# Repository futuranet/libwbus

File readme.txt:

== Disclaimer ==

This document contains information that might be wrong, not serve any
purpose or perhaps cause direct or indirect damage to any person. I cannot
be held responsible for anything in regard to this text document, the
accompanied documents or anything else related. Its all your own fault.

Any reference to any trade mark mentioned here or in the accompanied
documents are owned by their corresponding owners.

== What is this ? ==

A collection of W-Bus related libraries and programs for x86 and embedded
microcontroller devices.

== What is W-Bus ? ==

W-Bus is the serial line protocol used by Webasto (tm) car parking and
suplemental heating devices to communicate to a remote control or timer
unit, and also to performe PC assisted diagnosis of the device. This
interface is available on many modern Webasto (tm) heater devices.

== What W-Bus devices are supported to communicate to ? ==

Basic packet communication to any W-Bus capable device should be feasible.
Command codes, addresses or transaction IDs (how name them ?) are only known
so far for Thermo Top V heater devices. Some data has been discovered in
regard to the "1533" timer command devices and in the source forge forum
somebody also found some data in regard to Telestart (tm) receivers. I do
not own such devices so I cannot test anything in regard to that. Software
patches to add support for other devices are gladly accepted as long as the
changes do not add extra resource costs to the existing functionality and do
not include any unnecessary changes. Any patch containing "beautifications"
or any non functional changes will land directly in /dev/null. Don't loose
the point ;)

== What hardware does this software iself run on ? ==

The libwbus library and all its bundled applications should run on x86 Posix
like environment and MSP430 microcontrollers out of the box. Windows support
without cygwin is somewhat supported but there are known missing/broken
things.
Adapting the software for other targets should not be that difficult, just
grab an existing implementation and change it as necessary. For the hardware
and platform specific parts there are source code files using ad hoc
suffixes, and these source code files are included from source code files
without that suffixes. Just take a look and you will find out that quickly.
Doing this way, its not required changing makefiles or anything else to
switch hardware/platform, and thus only compiler built in macros should be
used to detect a given hardware or platform.

== K-Line adapter hardware ==
A K-Line is nothing but a single line serial connection, using a open
colector transistor that pulls a 12 Volt line to ground for mark bits.
At iddle, the line is at 12 Volt. As a pull up, 1Kohm should work ok.
See k_line.png for an example. The nets marked as TX and RX go to the
corresponding microcontroller serial port pins. The schematic shows an
example where the uC has 3.3 Volt I/O. You may need to adapt the voltage
levels depending on what hardware you do use.

== What is that Can-Bus thing ? ==

CAN-BUS is a network protocol for Controller Area Networks (hence the name).
It is widely used in the automotive world for communication between
different controller equipments.
Some people say that some Webasto (tm) devices can't be accessed through
W-Bus but only Can-Bus. That is not true, those devices are programmed at
the factory as suplemental heaters only, thus wont accept a parking heater
command on the W-Bus wire, but all others.
Possibly the reason is to avoid any cheap upgrade to a parking heater being
done by smart customers. Depending on for which car the heater was intended
the parking heater functionality might be enabled or not. From the hardware
perspective suplemental heaters and parking heater are identical AFAIK. The
firmware is different; this can be observed in the "W-Bus code" number.
Some car manufacturers sell upgrade packages which include a single use
dongle to enable parking heater functionality in suplemental heaters.

== Do you have a crack for the upgrade software dongle ? ==

No, I do not.
Its much easier to sell a suplemental heater on some auction house and buy
a parking heater for the same money.

== What is included in the repository ? ==

This software package comprises the following programs:

- openegg: W-Bus heater control unit targeted to a slightly modified MTK449
  olimex kit board. Schematics available on request, but I'm planning to
  rework the hardware at some point, but also using a MSP430 uC.
    The device when completely assembled provides through a menu driven UI the
  possibility to set 3 timers to turn on a W-Bus heater device. It also
  allows to select the command to be used, either parking heating,
  suplemental heating or ventilation.
  The heater can be turned on explicitly as well.
    Also it includes the function to connect a GSM mobile phone supporting
  the caller-ID AT commands, to program upto to 4 phone numbers to be
  authorized to turn on a W-Bus heater by calling the connected GSM mobile
  phone. The phone wont pick up the call, merely read out the caller ID number,
  thus no phone cost should ocurr.

- util/wbtool: a command line tool intended to be used on a PC or similar posix
  compatible system, to interact with a W-Bus device. Currently it supports
  all libwbus commands, thus turn on/off heater, read sensors, device ID
  data, etc.

- util/wbsim: a rudimentary and simple W-Bus device simulator mostly useful for
  understanding W-Bus and testing. In the W-Bus sense, its the counter part
  of wbtool.

- poeli: This program is intended to be used on an embedded heater device
  controller. It is designed for syphon nozzle atomizing burners with a
  nozzle stock heater, glow plug for ignition and flame monitoring,
  combustion air fan, nozzle air pressure compressor, 2 temperatur sensors,
  heat exchanger circulation pump, pulsed fuel pump (as usual in parking
  heaters), vehicle cabin fan output, and an auxiliar output. It acts as a
  W-Bus heater device, thus can be controlled and monitored using the
  Webasto (tm) Data Top (tm) software.
  A sequencer which is programmable via W-Bus protocol as well defines the
  course of action once a "heater on" or ventilation command is issued. Also
  the regular W-Bus component test commands and CO2 calibration are
  supported. The "program" can also be built and run on a PC for simulation
  purposes. See htsim.
  Circuit schematics are not included in the repository, and I'm not sure if
  I should really publish them. If you have any interest building a heater
  device, post it in the source forge forum, maybe there is some way to help
  you in that case. Heater device do burn fuel producing some kilo watt of
  heat and thus are DANGEROUS. Unless you plan to do something really stupid
  you are better off buying a ready made heater, building one is by far more
  expensive (easily a factor 4 of the price of an off the shelf device).

- bin/htsim: Heater device sensor / actuator simulator. A very simple basic
  and inaccurate model of a heater device. It uses shared memory to communicate
  to an instance of "poeli". It takes actuator values and generates data for
  the sensors. For example if the fuel pump is turned on, the simulator
  assumes combustion and will slowly rise the water temperatur sensor value
  and flame detector.

- util/htsim_gui: Same as htsim but interactive. Allows changing sensor
  values and watching actuator values via shared memory from an instance of
  "poeli". Since clicking on scrollbars takes a lot of time, rather less
  usefull. I never used it really, htsim turned out to be much more
  practical. Uses GTK+ and glade. Must be run from the "util" directory in
  order that the program can find its GUI description XML file.

- util/seq_edit: This programm allows to change almost all parameters of the
  poeli sequencer and read and write them via W-Bus to a heater device. This
  is not compatible with original Webasto (tm) heaters, since I do not know if
  and how they can be reprogrammed in this sense.

Libraries and others:

- libwbus: the wbus protocol handling library. see include/wbus.h for the
  client side API and include/wbus_server.h for the server side API.

- kernel: small cooperative multitasking micro kernel, to enable small
  microcontrollers to execute several tasks and blocking i/o. It also
  manages hardware abstraction in order to minimize the effort to port the
  whole software package to other processor architectures. Only 2-3 hardware
  specific lines of code.

- util/serial_loop: Linux kernel module which simulates 8 serial ports,
  which are looped back pairwise. It supports optional local echo, as it
  is the case in a K-Line or W-Bus line. It creates 8 device nodes called
  /dev/ttySL0 upto /dev/ttySL7, where /dev/ttySL0 is linked with
  /dev/ttySL1, and /dev/ttySL2 with /dev/ttySL3 and so on.
  The module should built with any recent 2.6 Linux kernel.

- Matlab files and excel spreadsheets: design blueprints and simulations
  that were used during the design and tuning of different parts of the
  heater device project. The Matlab files can be run directly as programs
  from a shell of GNU/Octave is installed.

== How do I compile this shit ? ==

Native compile:

make

Cross compile for MSP430f169:

make ARCH=msp430x169

To compile with debug symbols add DEBUG=1 to the command line.

the executables will be placed in bin<architecture name>, thus in
"binmsp430x169" for the example above. In case of native built in the folder
"bin".

The seq-edit and htsim_gui executables will be placed in util/ by the make
file, since it requires to load an XML file which is located there. Those
programs should be executed using util/ as working directory as well.

== How do I port this to my favorit uC since I hate that shitty MSP430 ? ==

- Re implement the functions and macros declared in the files rs232.h and
machine.h for your uC. Take the "posix" built variant as a template.
- Then put the implemention of that functions in new files called
rs232_myuc.c and machine_myuc.c. Where "myuc" somehow identifies your new uC
architechture or built environment. For example rs232_avr.c ...
- Make sure that those files are inluded in rs232.c and machine.c in case
your compiler for your uC is being used (consult predefined macros of your
compiler)
- Change the the Makefile CFLAGS and LDFLAGS if required.
- If you do not break functionality nor compilability for all other
architectures I might include the changes into CVS if you want that. If you
change anything out of scope, I wont do that.

If you are completely lost, don't start whining but improve your skills. You
might have to be pacient for that occurring of course, and have fun doing that :)

W-Bus version: 3.3
Device Name: PQ35 ZH 
W-Bus code: 213cc0e73f0000
Device ID Number: 0900620743
Data set ID Number: 090074764500
Software ID Number: 0000000030
Hardware version: 38/2
Software version: Monday 16/3  4.7
Software version EEPROM: Monday 16/3  4.7
Date of Manufacture Control Unit: 14.9.3
Date of Manufacture Heater: 1.10.3
Customer ID Number: 1K0815071E 0707
Serial Number: 0000349144
Sensor8: 42f0d004081858
U1: 0b0000000003bf
System Level: 58

== How was that damn command line to program my heater device ? ==

LIBMSPGCC_PATH=/usr/local/lib /home/mjander/source/msp430/python/msp430-jtag.py -e binmsp430x149/poeli

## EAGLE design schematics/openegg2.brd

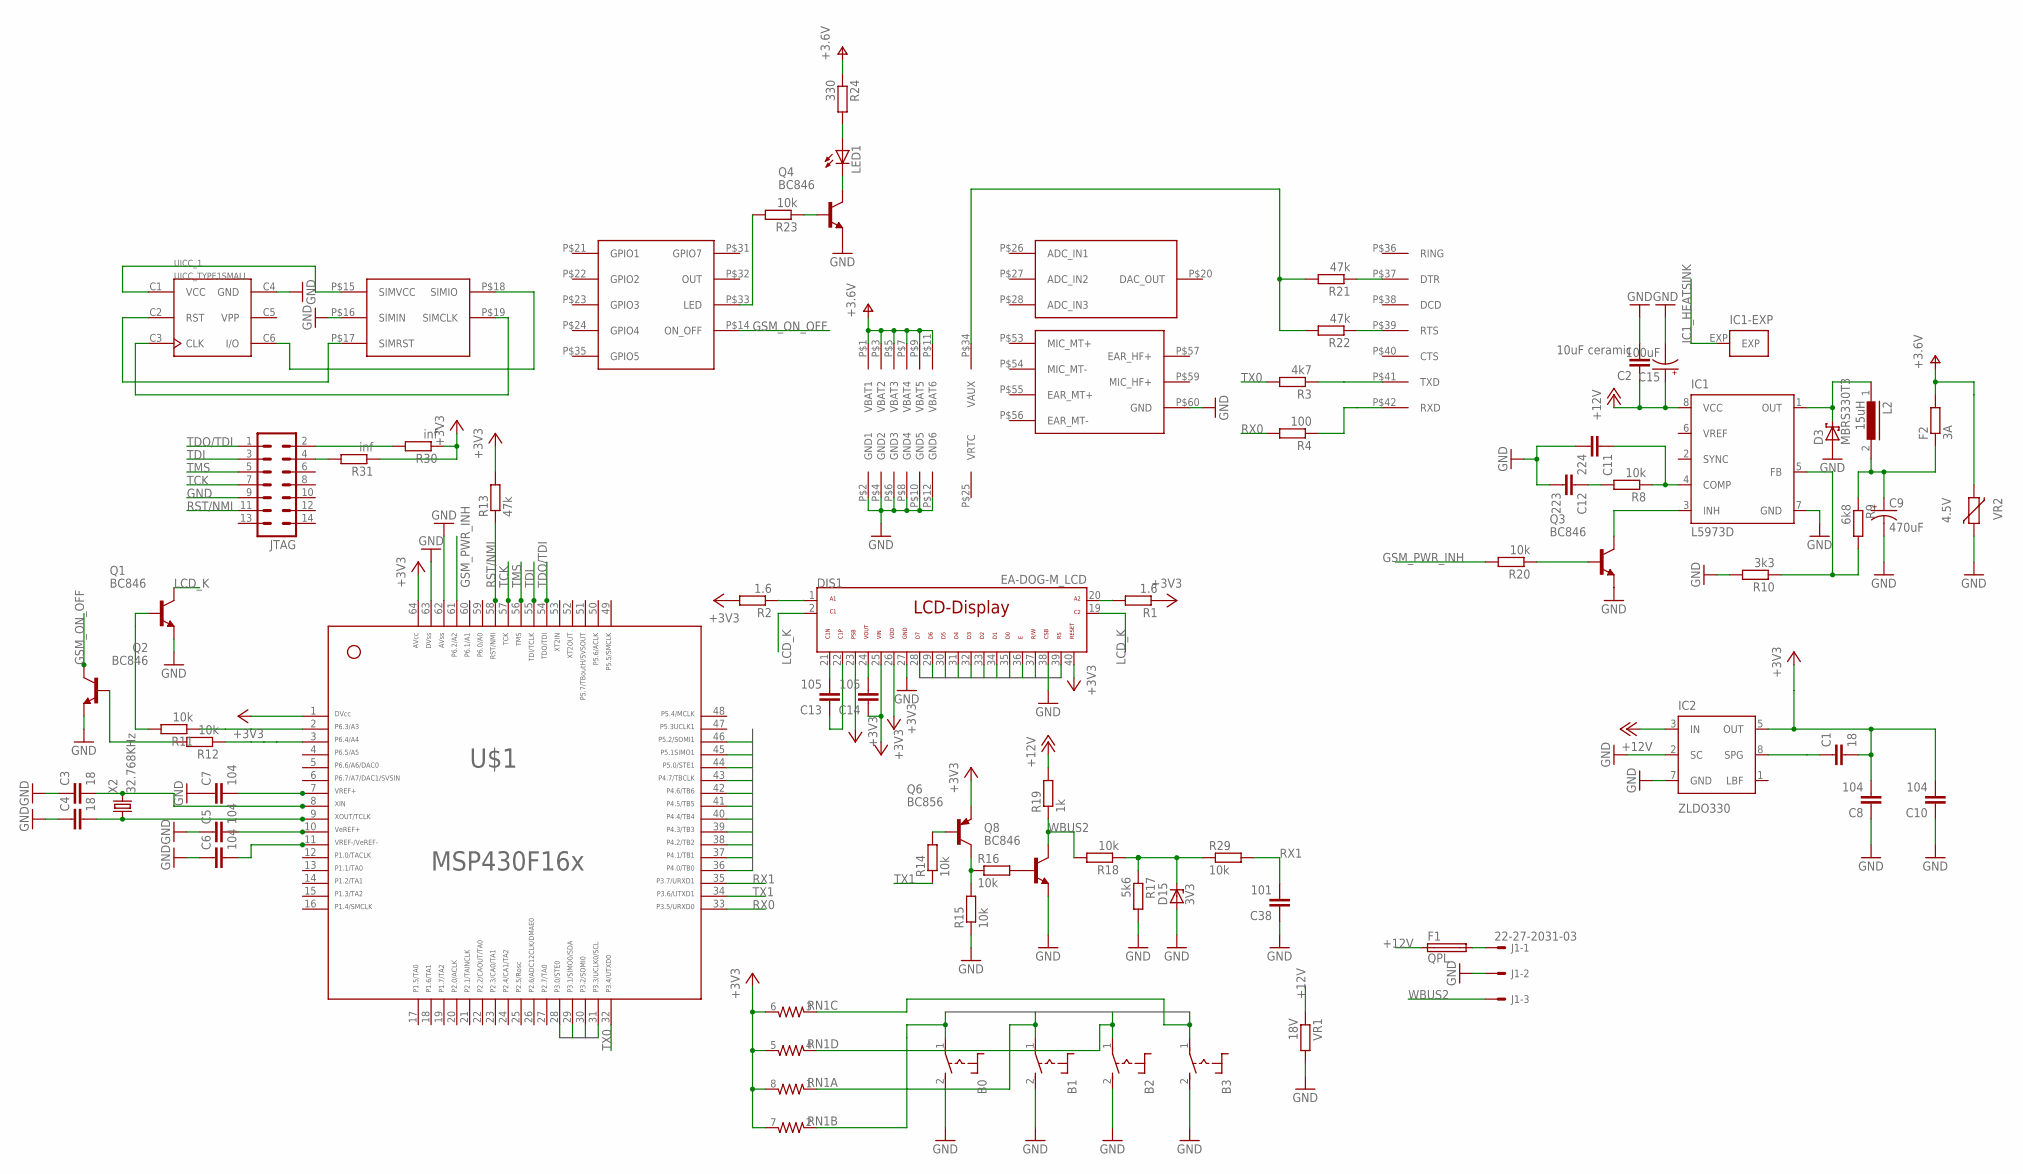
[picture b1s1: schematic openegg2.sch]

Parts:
B0, B1, B2, B3: MARQ6424; MARQ6424_NOLED
C1, C3, C4: 18; C0603
C2: 10uF ceramic; C1210K
C5, C6, C7: 104; C0603
C8, C10: 104; C1206
C9: 470uF; CT7343
C11: 224; C0402
C12: 223; C0402
C13, C14: 105; C1206
C15: 100uF; 153CLV-0505
C38: 101; C0402
D3: MBRS330T3; SMC
D15: 3V3; SOD80C
DIS1: EA-DOG-M_LCD
F1: QPL
F2: 3A; R2010
IC1: L5973D; HSOP8
IC2: ZLDO330; SM8
J1: 22-27-2031-03; 6410-03
JTAG: MA07-2
L2: 15uH; DR127
LED1: LEDCHIP-LED0603; CHIP-LED0603
Q1, Q2, Q3, Q4, Q8: BC846; SOT23
Q6: BC856; SOT23-BEC
R1, R2: 1.6; R1206
R3: 4k7; R0603
R4: 100; R0603
R8, R11, R12, R14, R15, R16, R18, R20, R23, R29: 10k; R0603
R9: 6k8; R0603
R10: 3k3; R0603
R13, R21, R22: 47k; R0603
R17: 5k6; R0603
R19: 1k; R0603
R24: 330; R0603
R30, R31: inf; R0603
RN1: 742-8_S; 742-8
U$1: F16X---PM64; PM/PAG64
U$2: GC864-QUAD-C2SMD; GC864-QUAD-C2_SMD
UICC_1: UICC_TYPE1SMALL; UICC_READER2
VR1: 18V; R2010
VR2: 4.5V; CT/CN1812
X2: 32.768KHz; TC26V

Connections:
+3V3: C1.2, C8.2, C10.2, C14.1, DIS1.23, DIS1.25, DIS1.26, DIS1.40, IC2.5 (OUT), Q6.E, R1.1, R2.2, R13.2, R30.1, R31.1, RN1.5 (2), RN1.6 (2), RN1.7 (2), RN1.8 (2), U$1.1, U$1.64
+12V: C2.1, C15.+, F1.1, IC1.8 (VCC), IC2.3 (IN), R19.2, VR1.1
B0: B0.1, RN1.2 (1), U$1.30
B1: B1.1, RN1.1, U$1.31
B2: B2.1, RN1.4 (1), U$1.28
B3: B3.1, RN1.3 (1), U$1.29
D0: DIS1.35, U$1.36
D1: DIS1.34, U$1.37
D2: DIS1.33, U$1.38
D3: DIS1.32, U$1.39
D4: DIS1.31, U$1.40
D5: DIS1.30, U$1.41
D6: DIS1.29, U$1.42
D7: DIS1.28, U$1.43
E: DIS1.36, U$1.45
GND: B0.2 (S), B1.2 (S), B2.2 (S), B3.2 (S), C2.2, C3.1, C4.1, C5.1, C6.1, C7.1, C8.1, C9.-, C10.1, C11.2, C12.2, C15.-, C38.1, D3.A, D15.A, DIS1.27, DIS1.38, IC1.7 (GND), IC2.2 (SC), IC2.7 (GND), J1.2, JTAG.9, Q1.2 (E), Q2.2 (E), Q3.2 (E), Q4.2 (E), Q8.2 (E), R10.2, R15.1, R17.2, U$1.62, U$1.63, U$2.P$2 (GND1), U$2.P$4 (GND2), U$2.P$6 (GND3), U$2.P$8 (GND4), U$2.P$10 (GND5), U$2.P$12 (GND6), U$2.P$16 (SIMIN), U$2.P$60 (GND), UICC_1.C4 (GND), VR1.2, VR2.1
GSM_ON_OFF: Q2.3 (C), U$2.P$14 (ON_OFF)
GSM_PWR_INH: R20.2, U$1.61
IC1_HEATSINK: IC1.EXP
LCD_K: DIS1.2, DIS1.19, Q1.3 (C)
unnamed: DIS1.1, R2.1
unnamed: DIS1.20, R1.2
unnamed: R3.1, U$2.P$41 (TXD)
unnamed: R4.1, U$2.P$42 (RXD)
unnamed: C1.1, IC2.8 (SPG)
unnamed: C4.2, U$1.9, X2.1
unnamed: JTAG.2, R30.2
unnamed: JTAG.4, R31.2
unnamed: IC1.5 (FB), R9.2, R10.1
unnamed: C9.+, F2.1, L2.2, R9.1
unnamed: D3.C, IC1.1 (OUT), L2.1
unnamed: C11.1, IC1.4 (COMP), R8.1
unnamed: C12.1, R8.2
unnamed: R11.1, U$1.2
unnamed: Q1.1 (B), R11.2
unnamed: R12.1, U$1.3
unnamed: Q2.1 (B), R12.2
unnamed: C13.2, DIS1.21
unnamed: C13.1, DIS1.22
unnamed: Q3.1 (B), R20.1
unnamed: C14.2, DIS1.24
unnamed: C3.2, U$1.8, X2.2
unnamed: Q6.B, R14.2
unnamed: Q6.C, R15.2, R16.1
unnamed: C5.2, U$1.10
unnamed: C6.2, U$1.11
unnamed: C7.2, U$1.7
unnamed: IC1.3 (INH), Q3.3 (C)
unnamed: Q8.1 (B), R16.2
unnamed: F1.2, J1.1
unnamed: R22.1, U$2.P$39 (RTS)
unnamed: R21.1, U$2.P$37 (DTR)
unnamed: R21.2, R22.2, U$2.P$34 (VAUX)
unnamed: R23.2, U$2.P$33 (LED)
unnamed: LED1.A, R24.2
unnamed: Q4.1 (B), R23.1
unnamed: LED1.C, Q4.3 (C)
NET$22: D15.C, R17.1, R18.1, R29.1
RS: DIS1.39, U$1.46
RST/NMI: JTAG.11, R13.1, U$1.58
RW: DIS1.37, U$1.44
RX0: R4.2, U$1.33
RX1: C38.2, R29.2, U$1.35
SIMCLK: U$2.P$19 (SIMCLK), UICC_1.C3 (CLK)
SIMIO: U$2.P$18 (SIMIO), UICC_1.C6 (I/O)
SIMRST: U$2.P$17 (SIMRST), UICC_1.C2 (RST)
SIMVCC: U$2.P$15 (SIMVCC), UICC_1.C1 (VCC)
TCK: JTAG.7, U$1.57
TDI: JTAG.3, U$1.55
TDO/TDI: JTAG.1, U$1.54
TMS: JTAG.5, U$1.56
TX0: R3.2, U$1.32
TX1: R14.1, U$1.34
V+: F2.2, R24.1, U$2.P$1 (VBAT1), U$2.P$3 (VBAT2), U$2.P$5 (VBAT3), U$2.P$7 (VBAT4), U$2.P$9 (VBAT5), U$2.P$11 (VBAT6), VR2.2
WBUS2: J1.3, Q8.3 (C), R18.2, R19.1

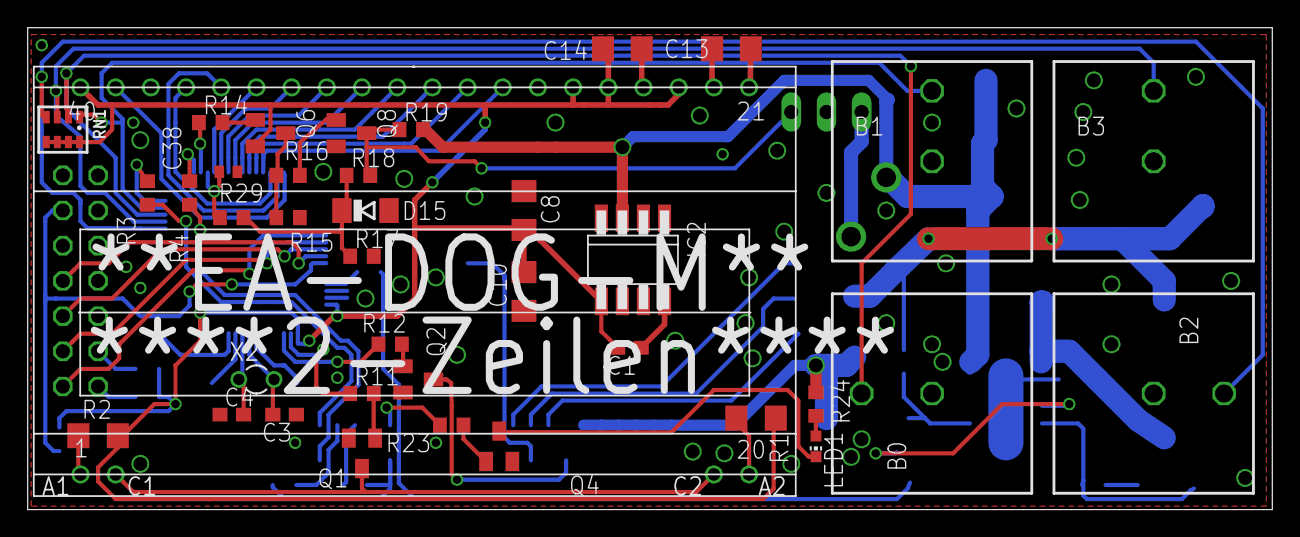
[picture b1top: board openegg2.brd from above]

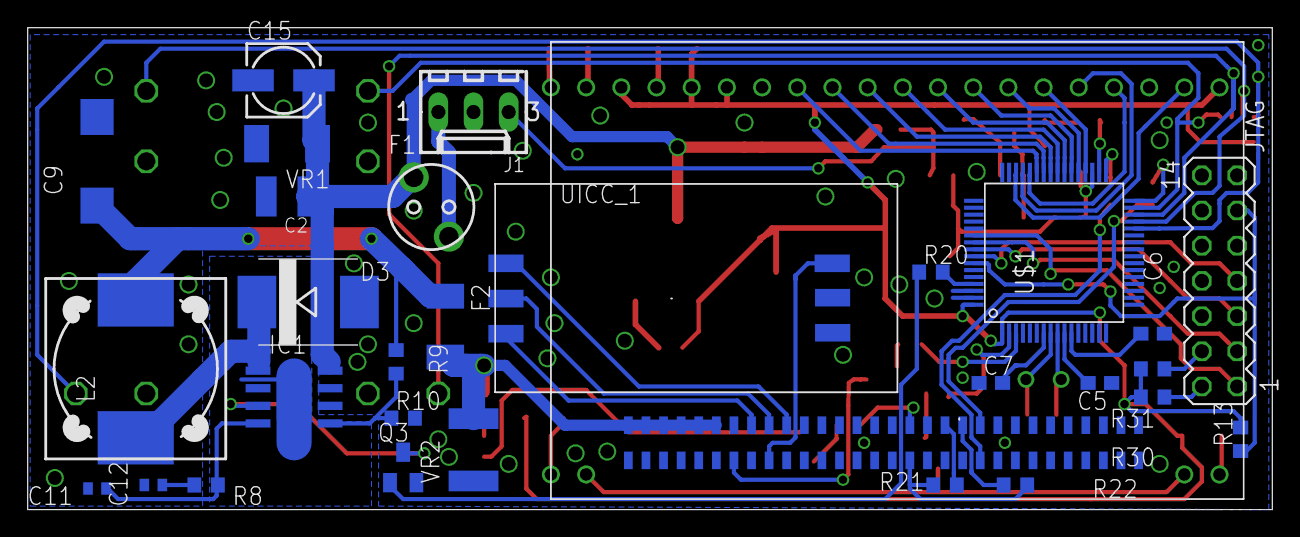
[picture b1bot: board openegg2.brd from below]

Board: 2 copper layers, 89.8 x 34.8 mm, 68 parts (30 on the bottom side), 74 nets.

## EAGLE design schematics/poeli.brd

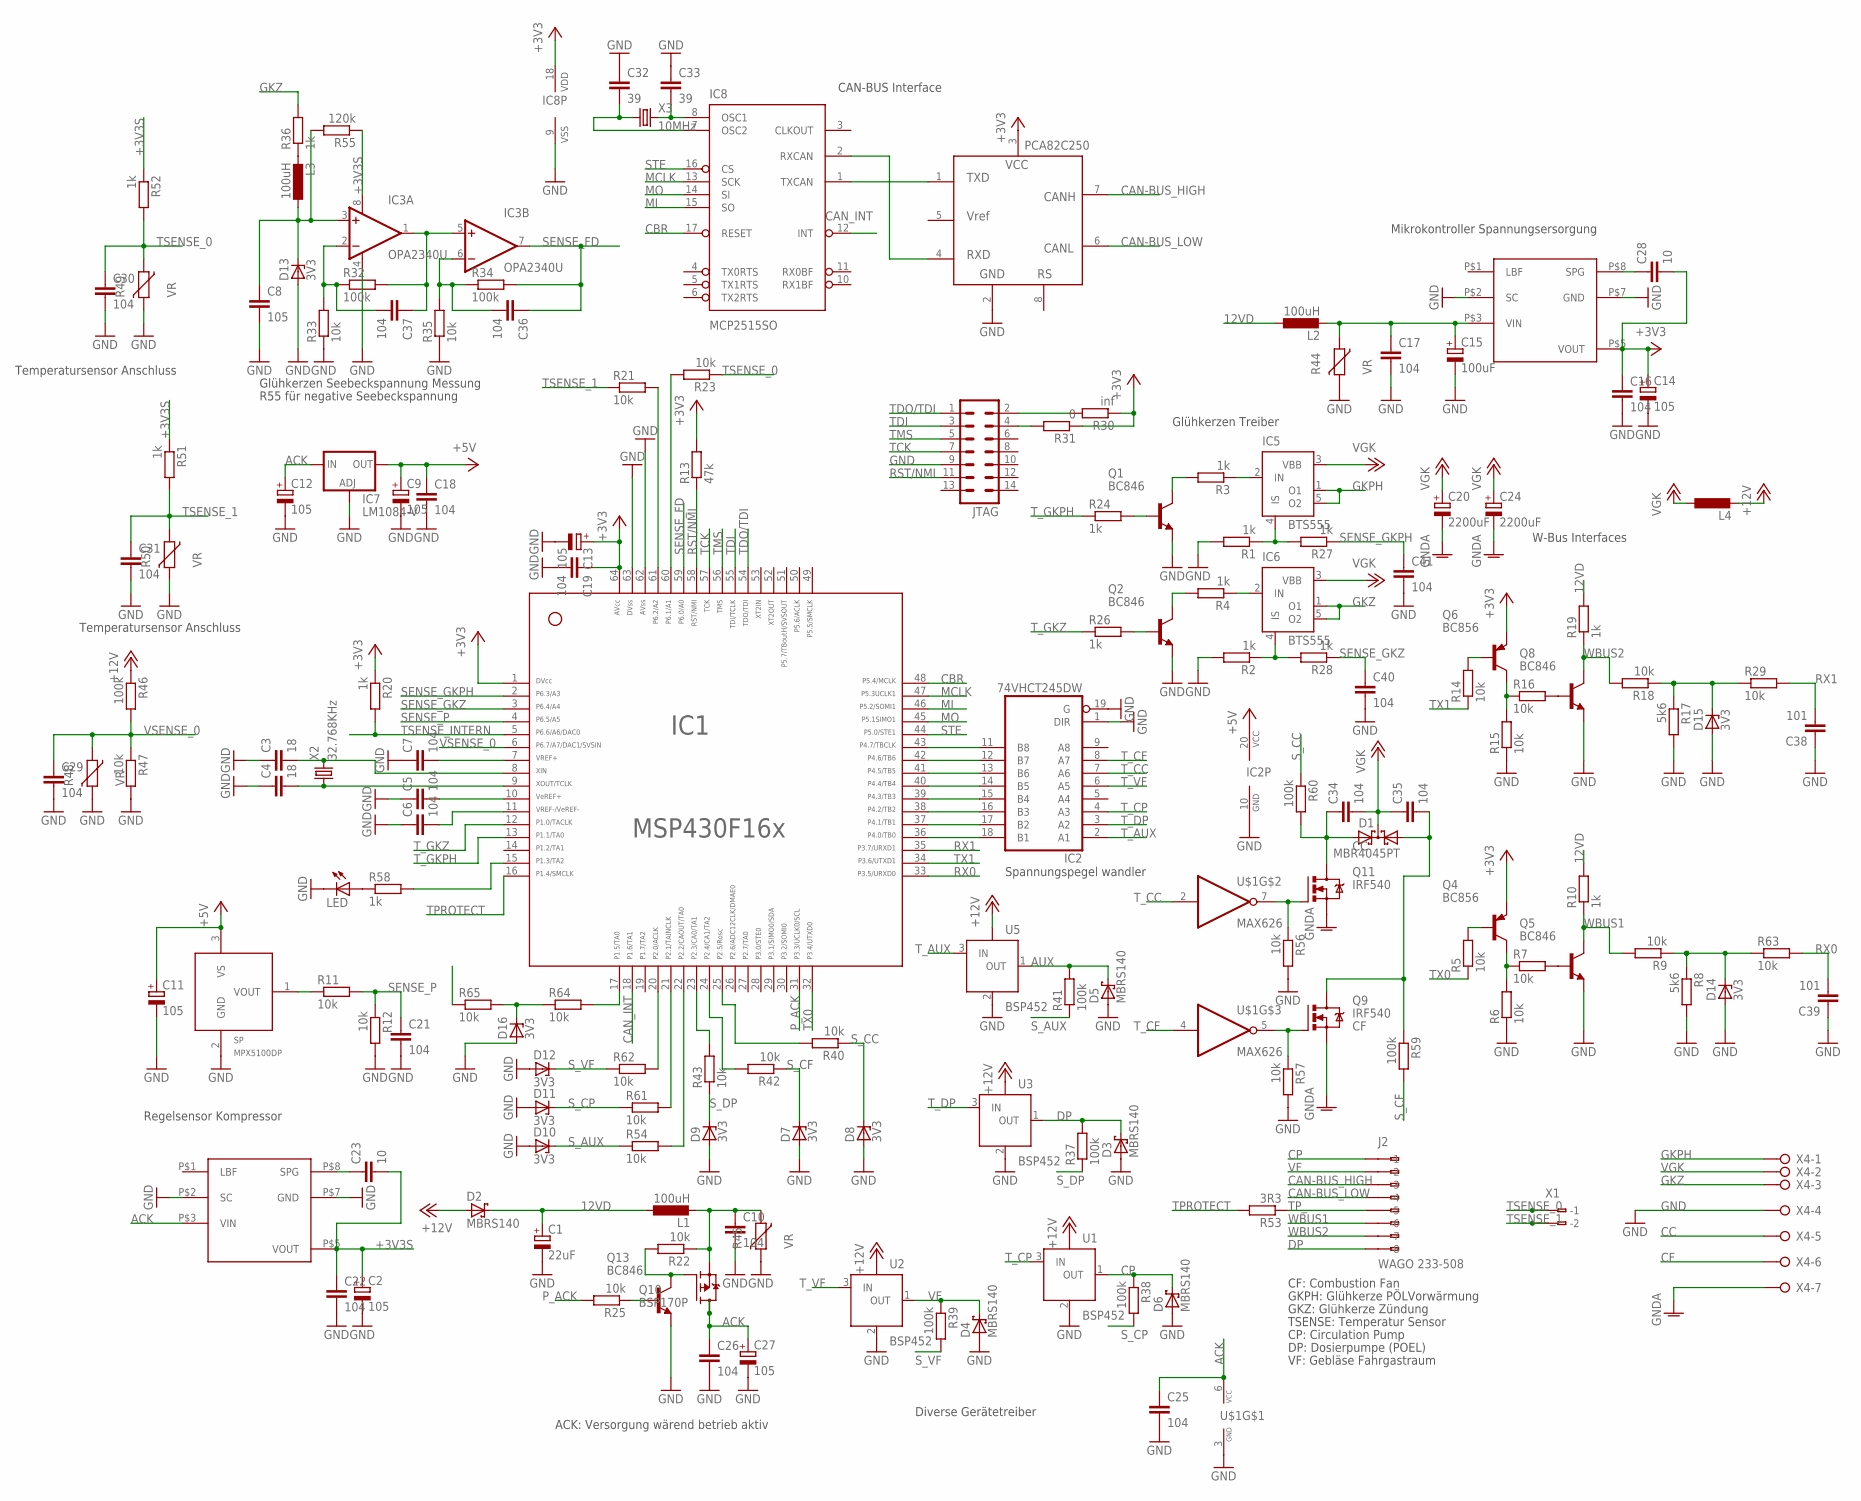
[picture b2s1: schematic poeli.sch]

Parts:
C1: 22uF; PANASONIC_C
C2, C9, C11, C12, C13, C14, C27: 105; UD-4X5,8_NICHICON
C3, C4: 18; C0603
C5, C6, C7, C36, C37, C40, C41: 104; C0603
C8: 105; C1206
C10, C18, C19, C26, C34, C35: 104; C1206
C15: 100uF; UD-6,3X7,7_NICHICON
C16, C17, C21, C29, C30, C31: 104; C0805K
C20, C24: 2200uF; SANYO-OSCON_G
C22: 104; C0603K
C23, C28: 10; C0603
C25: 104; C0805
C32, C33: 39; C0603
C38, C39: 101; C0402
D1: MBR4045PT; SOT93S
D2, D3, D4, D5, D6: MBRS140; SMB
D7, D8, D9, D10, D11, D12, D13, D14, D15, D16: 3V3; SOD80C
IC1: F169; PM/PAG64
IC2: 74VHCT245DW; SO20W
IC3: OPA2340U; SO08
IC4, IC10: ZLDO330; SM08
IC5, IC6: BTS555; TO220-51
IC7: LM1084-V; 317TS
IC8: MCP2515SO; SO-18W
IC9: PAC82C250
J2: WAGO 233-508; 233-508
JTAG: MA07-2
L1: 100uH; PIS2816
L2, L3: 100uH; L2825P
L4: L-EUL1812; L1812
LED: LEDCHIP-LED0603; CHIP-LED0603
Q1, Q2, Q5, Q8, Q13: BC846; SOT23
Q4, Q6: BC856; SOT23-BEC
Q9, Q11: IRF540; TO220BV
Q10: BSP170P; SOT223
R1, R2, R3, R4, R10, R19, R20, R24, R26, R27, R28, R36, R51, R52, R58: 1k; R0603
R5, R6, R7, R9, R11, R12, R14, R15, R16, R18, R21, R23, R25, R29, R33, R35, R40, R42, R43, R54, R61, R62, R63, R64, R65: 10k; R0603
R8, R17: 5k6; R0603
R13: 47k; R0603
R22, R47, R56, R57: 10k; R0805
R30: inf; R0603
R31: 0; R0603
R32, R34, R37, R38, R39, R41, R59, R60: 100k; R0603
R44, R45: VR; CT/CN1206
R46: 100k; R0805
R48, R49, R50: VR; CT/CN0603
R53: 3R3; R0805
R55: 120k; R1206
SP: MPX5100DP
U1, U2, U3, U5: BSP452; SOT223
U$1: MAX626; SO08
X1: 233-502
X2: 32.768KHz; TC26V
X3: 10MHz; CTS406
X4: W237-07P; W237-7P

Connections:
12VD: C1.+, D2.C, L1.1, L2.1, R10.2, R19.2
+3V3: C13.+, C14.+, C16.1, C19.1, C28.2, IC1.1, IC1.64, IC8.18 (VDD), IC9.3 (VCC), IC10.P$5 (VOUT), Q4.E, Q6.E, R13.2, R20.1, R30.1, R31.1
+3V3S: C2.+, C22.1, C23.2, IC3.8 (V+), IC4.P$5 (VOUT), R51.1, R52.1, R55.1
+5V: C9.+, C11.+, C18.1, IC2.20 (VCC), IC7.2 (OUT), SP.3 (VS)
+12V: D2.A, L4.1, L4.2, R46.1, U1.4 (VBB), U2.4 (VBB), U3.4 (VBB), U5.4 (VBB)
ACK: C12.+, C25.1, C26.1, C27.+, IC4.P$3 (VIN), IC7.3 (IN), Q10.2 (D), Q10.4 (D1), U$1.6 (VCC)
AUX: D5.C, R41.2, U5.1 (OUT)
CAF_RPS_INPUT: R65.1
CAN-BUS_HIGH: IC9.7 (CANH), J2.A3 (-3)
CAN-BUS_LOW: IC9.6 (CANL), J2.A4 (-4)
CAN_INT: IC1.18, IC8.12 (INT)
CBR: IC1.48, IC8.17 (RESET)
CC: C34.1, D1.A2, Q11.D, R60.2, X4.5
CF: C35.2, D1.A1, Q9.D, R59.1, X4.6
CP: D6.C, J2.A1 (-1), R38.1, U1.1 (OUT)
DP: D3.C, J2.A8 (-8), R37.2, U3.1 (OUT)
GKPH: IC5.1 (O1), IC5.5 (O2), X4.1
GKZ: IC6.1 (O1), IC6.5 (O2), R36.2, X4.3
GND: C1.-, C2.-, C3.1, C4.1, C5.1, C6.1, C7.1, C8.2, C9.-, C10.2, C11.-, C12.-, C13.-, C14.-, C15.-, C16.2, C17.2, C18.2, C19.2, C21.2, C22.2, C25.2, C26.2, C27.-, C29.2, C30.2, C31.2, C32.1, C33.1, C38.1, C39.1, C40.2, C41.2, D3.A, D4.A, D5.A, D6.A, D7.A, D8.A, D9.A, D10.A, D11.A, D12.A, D13.A, D14.A, D15.A, D16.A, IC1.62, IC1.63, IC2.1 (DIR), IC2.10 (GND), IC2.19 (G), IC3.4 (V-), IC4.P$2 (SC), IC4.P$7 (GND), IC7.1 (ADJ), IC8.9 (VSS), IC9.2 (GND), IC10.P$2 (SC), IC10.P$7 (GND), JTAG.9, LED.C, Q1.2 (E), Q2.2 (E), Q5.2 (E), Q8.2 (E), Q13.2 (E), R1.2, R2.2, R6.1, R8.2, R12.2, R15.1, R17.2, R33.1, R35.1, R44.2, R45.2, R47.2, R48.2, R49.2, R50.2, R56.2, R57.2, SP.2 (GND), U1.2 (GND), U2.2 (GND), U3.2 (GND), U5.2 (GND), U$1.3 (GND), X4.4
GNDA: C20.-, C24.-, Q9.S, Q11.S, X4.7
MCLK: IC1.47, IC8.13 (SCK)
MI: IC1.46, IC8.15 (SO)
MO: IC1.45, IC8.14 (SI)
unnamed: IC8.1 (TXCAN), IC9.1 (TXD)
unnamed: IC6.4 (IS), R2.1, R28.2
unnamed: Q1.3 (C), R3.2
unnamed: Q2.3 (C), R4.2
unnamed: IC1.43, IC2.11 (B8)
unnamed: IC5.2 (IN), R3.1
unnamed: C4.2, IC1.9, X2.1
unnamed: JTAG.2, R30.2
unnamed: JTAG.4, R31.2
unnamed: IC5.4 (IS), R1.1, R27.2
unnamed: IC1.42, IC2.12 (B7)
unnamed: IC1.41, IC2.13 (B6)
unnamed: IC1.40, IC2.14 (B5)
unnamed: Q2.1 (B), R26.2
unnamed: IC6.2 (IN), R4.1
unnamed: Q1.1 (B), R24.2
unnamed: Q4.B, R5.2
unnamed: R11.1, SP.1 (VOUT)
unnamed: Q4.C, R6.2, R7.1
unnamed: Q5.1 (B), R7.2
unnamed: C23.1, IC4.P$8 (SPG)
unnamed: D14.C, R8.1, R9.1, R63.1
unnamed: IC1.39, IC2.15 (B4)
unnamed: IC1.38, IC2.16 (B3)
unnamed: LED.A, R58.1
unnamed: C3.2, IC1.8, X2.2
unnamed: Q6.B, R14.2
unnamed: Q6.C, R15.2, R16.1
unnamed: C5.2, IC1.10
unnamed: C6.2, IC1.11
unnamed: C7.2, IC1.7
unnamed: IC1.17, R64.2
unnamed: Q8.1 (B), R16.2
unnamed: IC1.37, IC2.17 (B2)
unnamed: C36.2, IC3.6 (-IN), R34.1, R35.2
unnamed: IC1.36, IC2.18 (B1)
unnamed: Q11.G, R56.1, U$1.7 (O)
unnamed: Q9.G, R57.1, U$1.5 (O)
unnamed: Q13.1 (B), R25.1
unnamed: C37.2, IC3.2 (-IN), R32.1, R33.2
unnamed: C8.1, D13.C, IC3.3 (+IN), L3.1, R55.2
unnamed: Q10.1 (G), Q13.3 (C), R22.2
unnamed: C37.1, IC3.1 (OUT), IC3.5 (+IN), R32.2
unnamed: L3.2, R36.1
unnamed: IC1.61, R21.2
unnamed: IC1.60, R23.2
unnamed: IC1.25, R40.2
unnamed: IC8.2 (RXCAN), IC9.4 (RXD)
unnamed: C33.2, IC8.8 (OSC1), X3.3 (2)
unnamed: IC1.24, R42.2
unnamed: IC1.23, R43.2
unnamed: IC1.22, R54.2
unnamed: IC1.21, R61.2
unnamed: IC1.20, R62.2
unnamed: D16.C, R64.1, R65.2
unnamed: C28.1, IC10.P$8 (SPG)
unnamed: C10.1, L1.2, Q10.3 (S), R22.1, R45.1
unnamed: C15.+, C17.1, IC10.P$3 (VIN), L2.2, R44.1
unnamed: C32.2, IC8.7 (OSC2), X3.1
unnamed: IC1.15, R58.2
NET$22: D15.C, R17.1, R18.1, R29.1
P_ACK: IC1.31, R25.2
RST/NMI: IC1.58, JTAG.11, R13.1
RX0: C39.2, IC1.33, R63.2
RX1: C38.2, IC1.35, R29.2
SENSE_FD: C36.1, IC1.59, IC3.7 (OUT), R34.2
SENSE_GKPH: C41.1, IC1.2, R27.1
SENSE_GKZ: C40.1, IC1.3, R28.1
SENSE_P: C21.1, IC1.4, R11.2, R12.1
STE: IC1.44, IC8.16 (CS)
S_AUX: D10.C, R41.1, R54.1
S_CC: D8.C, R40.1, R60.1
S_CF: D7.C, R42.1, R59.2
S_CP: D11.C, R38.2, R61.1
S_DP: D9.C, R37.1, R43.1
S_VF: D12.C, R39.2, R62.1
TCK: IC1.57, JTAG.7
TDI: IC1.55, JTAG.3
TDO/TDI: IC1.54, JTAG.1
TMS: IC1.56, JTAG.5
TPROTECT: IC1.16, R53.2
TP_: J2.A5 (-5), R53.1
TSENSE_0: C30.1, R23.1, R49.1, R52.2, X1.A1 (-1), X1.B1 (B-1)
TSENSE_1: C31.1, R21.1, R50.1, R51.2, X1.A2 (-2), X1.B2 (B-2)
TSENSE_INTERN: IC1.5, R20.2
TX0: IC1.32, R5.1
TX1: IC1.34, R14.1
T_AUX: IC2.2 (A1), U5.3 (IN)
T_CC: IC2.7 (A6), U$1.2 (I)
T_CF: IC2.8 (A7), U$1.4 (I)
T_CP: IC2.4 (A3), U1.3 (IN)
T_DP: IC2.3 (A2), U3.3 (IN)
T_GKPH: IC1.13, R24.1
T_GKZ: IC1.12, R26.1
T_VF: IC2.6 (A5), U2.3 (IN)
VF: D4.C, J2.A2 (-2), R39.1, U2.1 (OUT)
VGK: C20.+, C24.+, C34.2, C35.1, D1.C, IC5.3 (VBB), IC6.3 (VBB), X4.2
VSENSE_0: C29.1, IC1.6, R46.2, R47.1, R48.1
WBUS1: J2.A6 (-6), Q5.3 (C), R9.2, R10.1
WBUS2: J2.A7 (-7), Q8.3 (C), R18.2, R19.1

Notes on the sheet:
DP: Dosierpumpe (POEL)
VF: Gebläse Fahrgastraum
CF: Combustion Fan
GKPH: Glühkerze PÖLVorwärmung
GKZ: Glühkerze Zündung
TSENSE: Temperatur Sensor
ACK: Versorgung wärend betrieb aktiv
Regelsensor Kompressor
CP: Circulation Pump
Spannungspegel wandler
Glühkerzen Seebeckspannung Messung
Temperatursensor Anschluss
CAN-BUS Interface
Mikrokontroller Spannungsersorgung
Glühkerzen Treiber
W-Bus Interfaces
Diverse Gerätetreiber
R55 für negative Seebeckspannung

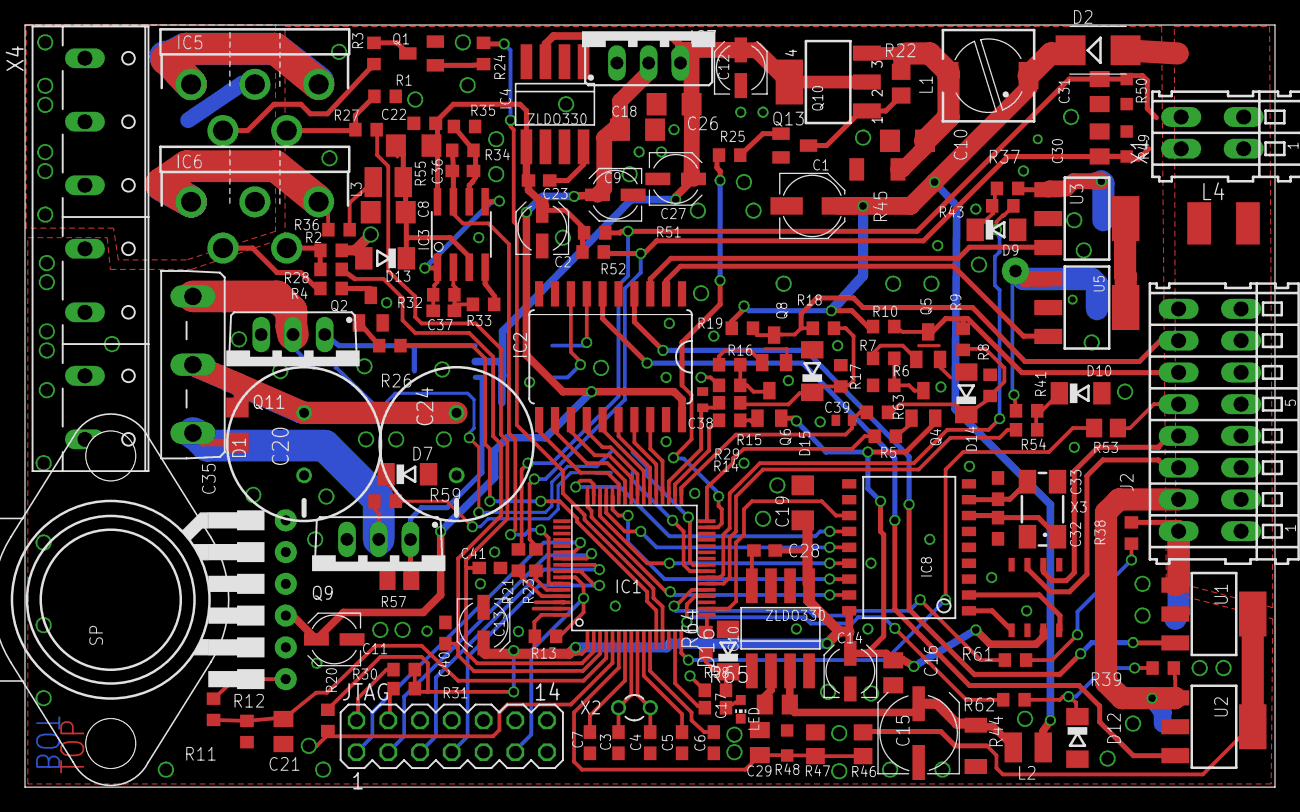
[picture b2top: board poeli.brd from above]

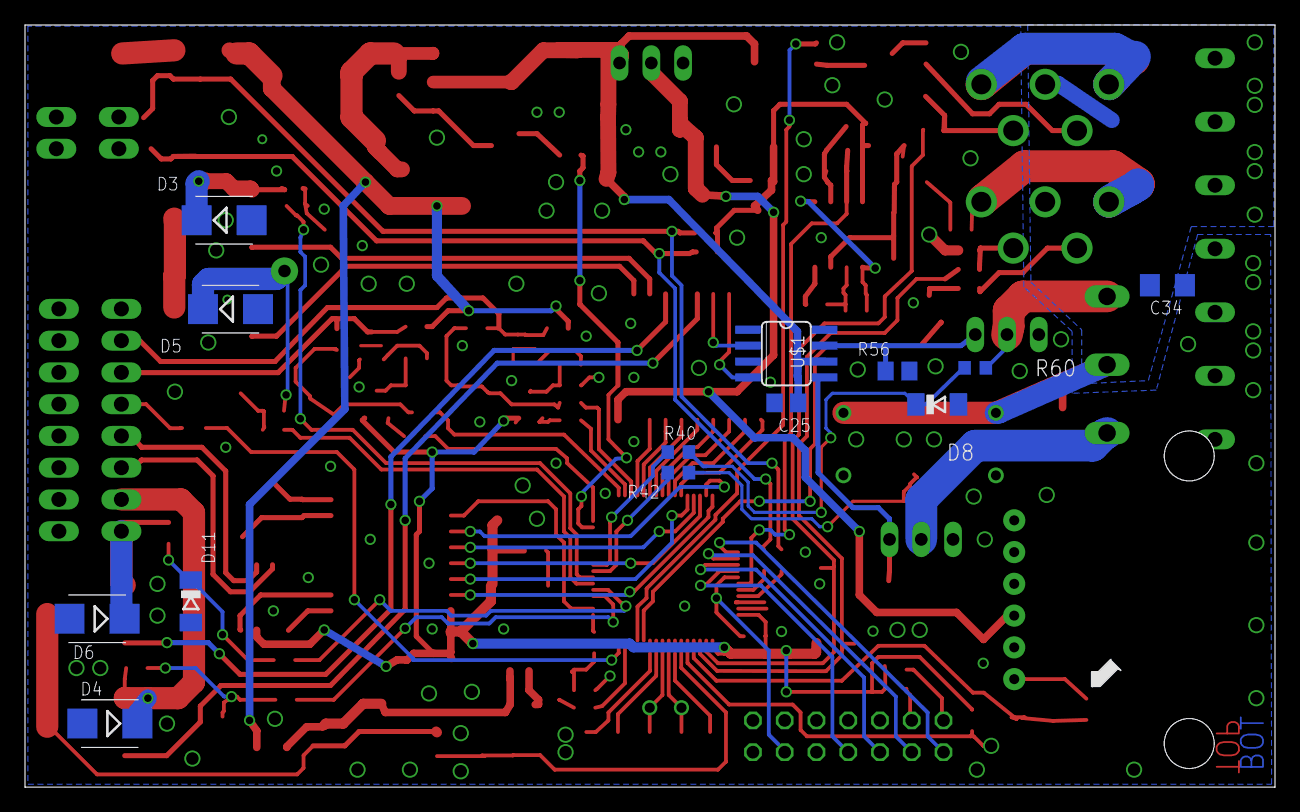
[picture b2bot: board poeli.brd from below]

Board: 2 copper layers, 100.0 x 61.0 mm, 159 parts (13 on the bottom side), 122 nets.

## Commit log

2014-01-18 Add user manual for openegg.
2014-10-08 Work in progress to add support for 2 hardware variants for egg.
2014-10-09 Fix LCD power control. Tested for MSP1x9 type hardware.
2014-10-10 Add GSM time update
2014-10-12 Add GSM nitz support Lots of small improvements
2014-10-13 Fix problem when writing to flash, miss of a timer interrupt and then the compare register value is just below the current timer counter, resulting in large delays until a task gets awake again.
    Merge configuration flash memory
2014-10-18 Add Backlight dimming. Fix error in nitz flash_write.
2014-10-27 Add old wbus docu
2014-10-29 Fix poeli issues due to hardware variant changes.
2014-11-13 Add schematics
2015-01-11 Add data set related commands
2015-01-11 Fix problem for egg hardware, where ADC interrupts with no ÍSR cause crash. Minor fixes.
2015-01-16 Add reception level and error rate to GSM status.
2015-01-16 Improve step down converter design for GSM module power.
2015-01-16 Undo wrong checkin
2015-02-06 Rename device to avoid conflict with software modems.
2015-02-06 Remove object files
2015-02-06 Route button pull up resistors.
2015-02-24 Some fixes for x86

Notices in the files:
parts and their libraries:
resistor-array: Copyright (C) 2008, Bob Starr
